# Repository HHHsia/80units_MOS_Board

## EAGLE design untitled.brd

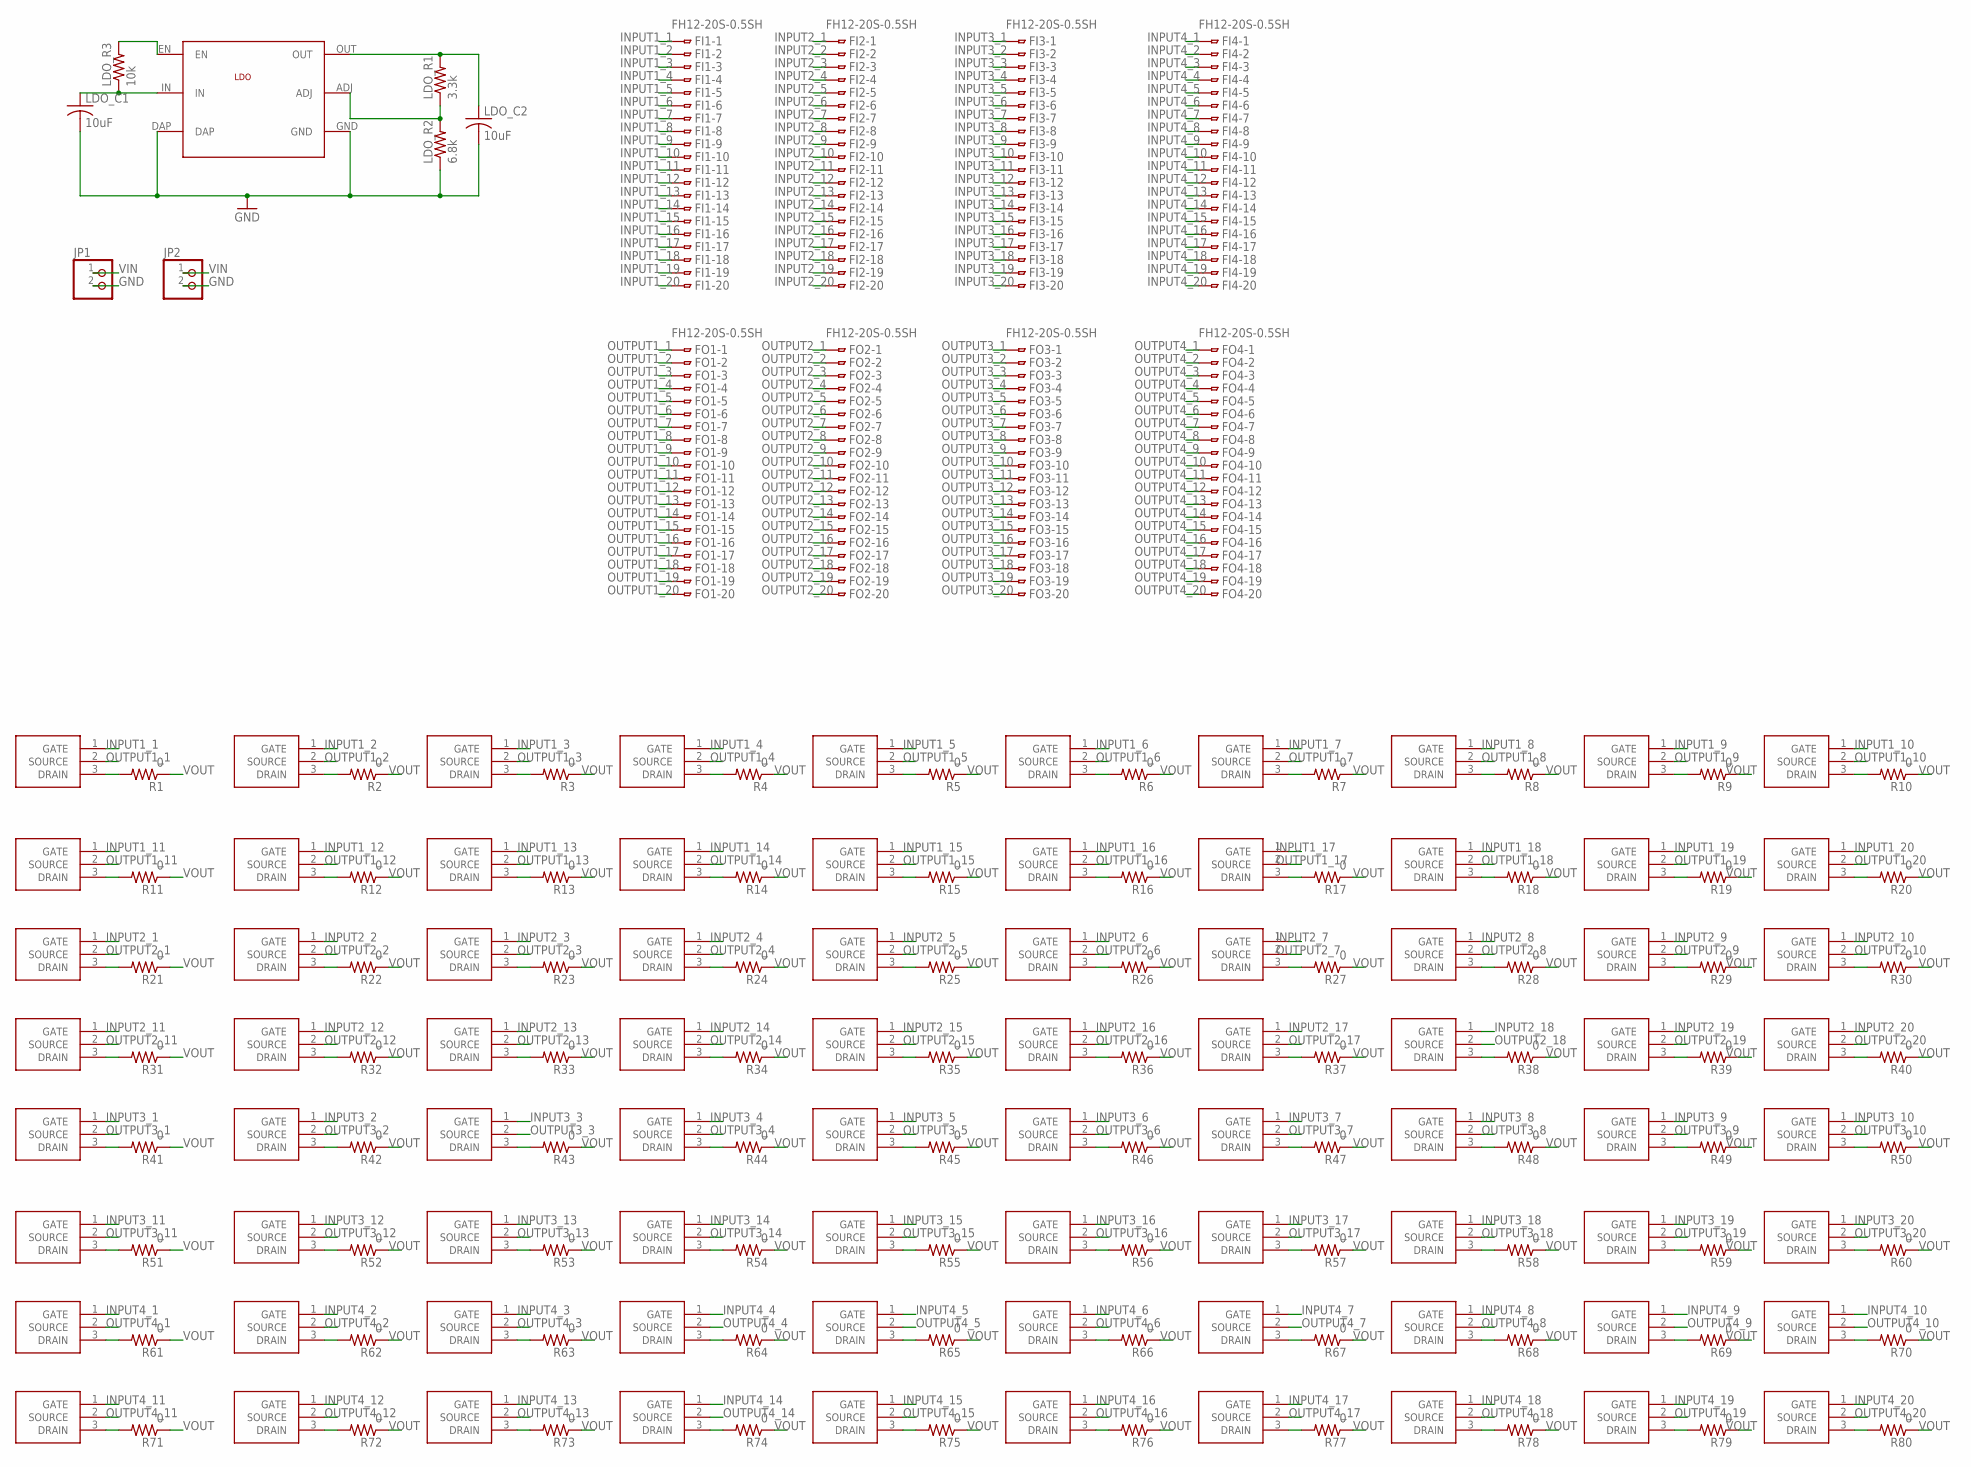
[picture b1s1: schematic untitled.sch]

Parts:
FI1, FI2, FI3, FI4: FH12-20S-0.5SH
FO1, FO2, FO3, FO4: FH12-20S-0.5SH
JP1, JP2: PINHD-1X2; 1X02
LDO: LP38501TS_ADJ
LDO_C1, LDO_C2: 10uF; C0805
LDO_R1: 3.3k; R0805
LDO_R2: 6.8k; R0805
LDO_R3: 10k; R0805
MOS1, MOS2, MOS3, MOS4, MOS5, MOS6, MOS7, MOS8, MOS9, MOS10, MOS11, MOS12, MOS13, MOS14, MOS15, MOS16, MOS17, MOS18, MOS19, MOS20, MOS21, MOS22, MOS23, MOS24, MOS25, MOS26, MOS27, MOS28, MOS29, MOS30, MOS31, MOS32, MOS33, MOS34, MOS35, MOS36, MOS37, MOS38, MOS39, MOS40, MOS41, MOS42, MOS43, MOS44, MOS45, MOS46, MOS47, MOS48, MOS49, MOS50, MOS51, MOS52, MOS53, MOS54, MOS55, MOS56, MOS57, MOS58, MOS59, MOS60, MOS61, MOS62, MOS63, MOS64, MOS65, MOS66, MOS67, MOS68, MOS69, MOS70, MOS71, MOS72, MOS73, MOS74, MOS75, MOS76, MOS77, MOS78, MOS79, MOS80: NX6008NBKNX6008NBK; SOT95P240X110-3N
R1, R2, R3, R4, R5, R6, R7, R8, R9, R10, R11, R12, R13, R14, R15, R16, R17, R18, R19, R20, R21, R22, R23, R24, R25, R26, R27, R28, R29, R30, R31, R32, R33, R34, R35, R36, R37, R38, R39, R40, R41, R42, R43, R44, R45, R46, R47, R48, R49, R50, R51, R52, R53, R54, R55, R56, R57, R58, R59, R60, R61, R62, R63, R64, R65, R66, R67, R68, R69, R70, R71, R72, R73, R74, R75, R76, R77, R78, R79, R80: 0; R0805

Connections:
GND: JP1.2, JP2.2, LDO.DAP, LDO.GND, LDO_C1.2, LDO_C2.2, LDO_R2.1
INPUT1_1: FI1.1, MOS1.1 (GATE)
INPUT1_2: FI1.2, MOS2.1 (GATE)
INPUT1_3: FI1.3, MOS3.1 (GATE)
INPUT1_4: FI1.4, MOS4.1 (GATE)
INPUT1_5: FI1.5, MOS5.1 (GATE)
INPUT1_6: FI1.6, MOS6.1 (GATE)
INPUT1_7: FI1.7, MOS7.1 (GATE)
INPUT1_8: FI1.8, MOS8.1 (GATE)
INPUT1_9: FI1.9, MOS9.1 (GATE)
INPUT1_10: FI1.10, MOS10.1 (GATE)
INPUT1_11: FI1.11, MOS11.1 (GATE)
INPUT1_12: FI1.12, MOS12.1 (GATE)
INPUT1_13: FI1.13, MOS13.1 (GATE)
INPUT1_14: FI1.14, MOS14.1 (GATE)
INPUT1_15: FI1.15, MOS15.1 (GATE)
INPUT1_16: FI1.16, MOS16.1 (GATE)
INPUT1_17: FI1.17, MOS17.1 (GATE)
INPUT1_18: FI1.18, MOS18.1 (GATE)
INPUT1_19: FI1.19, MOS19.1 (GATE)
INPUT1_20: FI1.20, MOS20.1 (GATE)
INPUT2_1: FI2.1, MOS21.1 (GATE)
INPUT2_2: FI2.2, MOS22.1 (GATE)
INPUT2_3: FI2.3, MOS23.1 (GATE)
INPUT2_4: FI2.4, MOS24.1 (GATE)
INPUT2_5: FI2.5, MOS25.1 (GATE)
INPUT2_6: FI2.6, MOS26.1 (GATE)
INPUT2_7: FI2.7, MOS27.1 (GATE)
INPUT2_8: FI2.8, MOS28.1 (GATE)
INPUT2_9: FI2.9, MOS29.1 (GATE)
INPUT2_10: FI2.10, MOS30.1 (GATE)
INPUT2_11: FI2.11, MOS31.1 (GATE)
INPUT2_12: FI2.12, MOS32.1 (GATE)
INPUT2_13: FI2.13, MOS33.1 (GATE)
INPUT2_14: FI2.14, MOS34.1 (GATE)
INPUT2_15: FI2.15, MOS35.1 (GATE)
INPUT2_16: FI2.16, MOS36.1 (GATE)
INPUT2_17: FI2.17, MOS37.1 (GATE)
INPUT2_18: FI2.18, MOS38.1 (GATE)
INPUT2_19: FI2.19, MOS39.1 (GATE)
INPUT2_20: FI2.20, MOS40.1 (GATE)
INPUT3_1: FI3.1, MOS41.1 (GATE)
INPUT3_2: FI3.2, MOS42.1 (GATE)
INPUT3_3: FI3.3, MOS43.1 (GATE)
INPUT3_4: FI3.4, MOS44.1 (GATE)
INPUT3_5: FI3.5, MOS45.1 (GATE)
INPUT3_6: FI3.6, MOS46.1 (GATE)
INPUT3_7: FI3.7, MOS47.1 (GATE)
INPUT3_8: FI3.8, MOS48.1 (GATE)
INPUT3_9: FI3.9, MOS49.1 (GATE)
INPUT3_10: FI3.10, MOS50.1 (GATE)
INPUT3_11: FI3.11, MOS51.1 (GATE)
INPUT3_12: FI3.12, MOS52.1 (GATE)
INPUT3_13: FI3.13, MOS53.1 (GATE)
INPUT3_14: FI3.14, MOS54.1 (GATE)
INPUT3_15: FI3.15, MOS55.1 (GATE)
INPUT3_16: FI3.16, MOS56.1 (GATE)
INPUT3_17: FI3.17, MOS57.1 (GATE)
INPUT3_18: FI3.18, MOS58.1 (GATE)
INPUT3_19: FI3.19, MOS59.1 (GATE)
INPUT3_20: FI3.20, MOS60.1 (GATE)
INPUT4_1: FI4.1, MOS61.1 (GATE)
INPUT4_2: FI4.2, MOS62.1 (GATE)
INPUT4_3: FI4.3, MOS63.1 (GATE)
INPUT4_4: FI4.4, MOS64.1 (GATE)
INPUT4_5: FI4.5, MOS65.1 (GATE)
INPUT4_6: FI4.6, MOS66.1 (GATE)
INPUT4_7: FI4.7, MOS67.1 (GATE)
INPUT4_8: FI4.8, MOS68.1 (GATE)
INPUT4_9: FI4.9, MOS69.1 (GATE)
INPUT4_10: FI4.10, MOS70.1 (GATE)
INPUT4_11: FI4.11, MOS71.1 (GATE)
INPUT4_12: FI4.12, MOS72.1 (GATE)
INPUT4_13: FI4.13, MOS73.1 (GATE)
INPUT4_14: FI4.14, MOS74.1 (GATE)
INPUT4_15: FI4.15, MOS75.1 (GATE)
INPUT4_16: FI4.16, MOS76.1 (GATE)
INPUT4_17: FI4.17, MOS77.1 (GATE)
INPUT4_18: FI4.18, MOS78.1 (GATE)
INPUT4_19: FI4.19, MOS79.1 (GATE)
INPUT4_20: FI4.20, MOS80.1 (GATE)
unnamed: LDO.EN, LDO_R3.2
unnamed: MOS77.3 (DRAIN), R77.2
unnamed: LDO.ADJ, LDO_R1.1, LDO_R2.2
unnamed: MOS1.3 (DRAIN), R1.2
unnamed: MOS2.3 (DRAIN), R2.2
unnamed: MOS3.3 (DRAIN), R3.2
unnamed: MOS4.3 (DRAIN), R4.2
unnamed: MOS5.3 (DRAIN), R5.2
unnamed: MOS6.3 (DRAIN), R6.2
unnamed: MOS7.3 (DRAIN), R7.2
unnamed: MOS8.3 (DRAIN), R8.2
unnamed: MOS9.3 (DRAIN), R9.2
unnamed: MOS10.3 (DRAIN), R10.2
unnamed: MOS11.3 (DRAIN), R11.2
unnamed: MOS12.3 (DRAIN), R12.2
unnamed: MOS13.3 (DRAIN), R13.2
unnamed: MOS14.3 (DRAIN), R14.2
unnamed: MOS15.3 (DRAIN), R15.2
unnamed: MOS16.3 (DRAIN), R16.2
unnamed: MOS17.3 (DRAIN), R17.2
unnamed: MOS18.3 (DRAIN), R18.2
unnamed: MOS19.3 (DRAIN), R19.2
unnamed: MOS20.3 (DRAIN), R20.2
unnamed: MOS21.3 (DRAIN), R21.2
unnamed: MOS22.3 (DRAIN), R22.2
unnamed: MOS23.3 (DRAIN), R23.2
unnamed: MOS24.3 (DRAIN), R24.2
unnamed: MOS25.3 (DRAIN), R25.2
unnamed: MOS26.3 (DRAIN), R26.2
unnamed: MOS27.3 (DRAIN), R27.2
unnamed: MOS28.3 (DRAIN), R28.2
unnamed: MOS29.3 (DRAIN), R29.2
unnamed: MOS30.3 (DRAIN), R30.2
unnamed: MOS31.3 (DRAIN), R31.2
unnamed: MOS32.3 (DRAIN), R32.2
unnamed: MOS33.3 (DRAIN), R33.2
unnamed: MOS34.3 (DRAIN), R34.2
unnamed: MOS35.3 (DRAIN), R35.2
unnamed: MOS36.3 (DRAIN), R36.2
unnamed: MOS37.3 (DRAIN), R37.2
unnamed: MOS38.3 (DRAIN), R38.2
unnamed: MOS39.3 (DRAIN), R39.2
unnamed: MOS40.3 (DRAIN), R40.2
unnamed: MOS41.3 (DRAIN), R41.2
unnamed: MOS42.3 (DRAIN), R42.2
unnamed: MOS43.3 (DRAIN), R43.2
unnamed: MOS44.3 (DRAIN), R44.2
unnamed: MOS45.3 (DRAIN), R45.2
unnamed: MOS46.3 (DRAIN), R46.2
unnamed: MOS47.3 (DRAIN), R47.2
unnamed: MOS48.3 (DRAIN), R48.2
unnamed: MOS49.3 (DRAIN), R49.2
unnamed: MOS50.3 (DRAIN), R50.2
unnamed: MOS51.3 (DRAIN), R51.2
unnamed: MOS52.3 (DRAIN), R52.2
unnamed: MOS53.3 (DRAIN), R53.2
unnamed: MOS54.3 (DRAIN), R54.2
unnamed: MOS55.3 (DRAIN), R55.2
unnamed: MOS56.3 (DRAIN), R56.2
unnamed: MOS57.3 (DRAIN), R57.2
unnamed: MOS58.3 (DRAIN), R58.2
unnamed: MOS59.3 (DRAIN), R59.2
unnamed: MOS60.3 (DRAIN), R60.2
unnamed: MOS61.3 (DRAIN), R61.2
unnamed: MOS62.3 (DRAIN), R62.2
unnamed: MOS63.3 (DRAIN), R63.2
unnamed: MOS64.3 (DRAIN), R64.2
unnamed: MOS65.3 (DRAIN), R65.2
unnamed: MOS66.3 (DRAIN), R66.2
unnamed: MOS67.3 (DRAIN), R67.2
unnamed: MOS68.3 (DRAIN), R68.2
unnamed: MOS69.3 (DRAIN), R69.2
unnamed: MOS70.3 (DRAIN), R70.2
unnamed: MOS71.3 (DRAIN), R71.2
unnamed: MOS72.3 (DRAIN), R72.2
unnamed: MOS73.3 (DRAIN), R73.2
unnamed: MOS74.3 (DRAIN), R74.2
unnamed: MOS75.3 (DRAIN), R75.2
unnamed: MOS76.3 (DRAIN), R76.2
unnamed: MOS78.3 (DRAIN), R78.2
unnamed: MOS79.3 (DRAIN), R79.2
unnamed: MOS80.3 (DRAIN), R80.2
OUTPUT1_1: FO1.1, MOS1.2 (SOURCE)
OUTPUT1_2: FO1.2, MOS2.2 (SOURCE)
OUTPUT1_3: FO1.3, MOS3.2 (SOURCE)
OUTPUT1_4: FO1.4, MOS4.2 (SOURCE)
OUTPUT1_5: FO1.5, MOS5.2 (SOURCE)
OUTPUT1_6: FO1.6, MOS6.2 (SOURCE)
OUTPUT1_7: FO1.7, MOS7.2 (SOURCE)
OUTPUT1_8: FO1.8, MOS8.2 (SOURCE)
OUTPUT1_9: FO1.9, MOS9.2 (SOURCE)
OUTPUT1_10: FO1.10, MOS10.2 (SOURCE)
OUTPUT1_11: FO1.11, MOS11.2 (SOURCE)
OUTPUT1_12: FO1.12, MOS12.2 (SOURCE)
OUTPUT1_13: FO1.13, MOS13.2 (SOURCE)
OUTPUT1_14: FO1.14, MOS14.2 (SOURCE)
OUTPUT1_15: FO1.15, MOS15.2 (SOURCE)
OUTPUT1_16: FO1.16, MOS16.2 (SOURCE)
OUTPUT1_17: FO1.17, MOS17.2 (SOURCE)
OUTPUT1_18: FO1.18, MOS18.2 (SOURCE)
OUTPUT1_19: FO1.19, MOS19.2 (SOURCE)
OUTPUT1_20: FO1.20, MOS20.2 (SOURCE)
OUTPUT2_1: FO2.1, MOS21.2 (SOURCE)
OUTPUT2_2: FO2.2, MOS22.2 (SOURCE)
OUTPUT2_3: FO2.3, MOS23.2 (SOURCE)
OUTPUT2_4: FO2.4, MOS24.2 (SOURCE)
OUTPUT2_5: FO2.5, MOS25.2 (SOURCE)
OUTPUT2_6: FO2.6, MOS26.2 (SOURCE)
OUTPUT2_7: FO2.7, MOS27.2 (SOURCE)
OUTPUT2_8: FO2.8, MOS28.2 (SOURCE)
OUTPUT2_9: FO2.9, MOS29.2 (SOURCE)
OUTPUT2_10: FO2.10, MOS30.2 (SOURCE)
OUTPUT2_11: FO2.11, MOS31.2 (SOURCE)
OUTPUT2_12: FO2.12, MOS32.2 (SOURCE)
OUTPUT2_13: FO2.13, MOS33.2 (SOURCE)
OUTPUT2_14: FO2.14, MOS34.2 (SOURCE)
OUTPUT2_15: FO2.15, MOS35.2 (SOURCE)
OUTPUT2_16: FO2.16, MOS36.2 (SOURCE)
OUTPUT2_17: FO2.17, MOS37.2 (SOURCE)
OUTPUT2_18: FO2.18, MOS38.2 (SOURCE)
OUTPUT2_19: FO2.19, MOS39.2 (SOURCE)
OUTPUT2_20: FO2.20, MOS40.2 (SOURCE)
OUTPUT3_1: FO3.1, MOS41.2 (SOURCE)
OUTPUT3_2: FO3.2, MOS42.2 (SOURCE)
OUTPUT3_3: FO3.3, MOS43.2 (SOURCE)
OUTPUT3_4: FO3.4, MOS44.2 (SOURCE)
OUTPUT3_5: FO3.5, MOS45.2 (SOURCE)
OUTPUT3_6: FO3.6, MOS46.2 (SOURCE)
OUTPUT3_7: FO3.7, MOS47.2 (SOURCE)
OUTPUT3_8: FO3.8, MOS48.2 (SOURCE)
OUTPUT3_9: FO3.9, MOS49.2 (SOURCE)
OUTPUT3_10: FO3.10, MOS50.2 (SOURCE)
OUTPUT3_11: FO3.11, MOS51.2 (SOURCE)
OUTPUT3_12: FO3.12, MOS52.2 (SOURCE)
OUTPUT3_13: FO3.13, MOS53.2 (SOURCE)
OUTPUT3_14: FO3.14, MOS54.2 (SOURCE)
OUTPUT3_15: FO3.15, MOS55.2 (SOURCE)
OUTPUT3_16: FO3.16, MOS56.2 (SOURCE)
OUTPUT3_17: FO3.17, MOS57.2 (SOURCE)
OUTPUT3_18: FO3.18, MOS58.2 (SOURCE)
OUTPUT3_19: FO3.19, MOS59.2 (SOURCE)
OUTPUT3_20: FO3.20, MOS60.2 (SOURCE)
OUTPUT4_1: FO4.1, MOS61.2 (SOURCE)
OUTPUT4_2: FO4.2, MOS62.2 (SOURCE)
OUTPUT4_3: FO4.3, MOS63.2 (SOURCE)
OUTPUT4_4: FO4.4, MOS64.2 (SOURCE)
OUTPUT4_5: FO4.5, MOS65.2 (SOURCE)
OUTPUT4_6: FO4.6, MOS66.2 (SOURCE)
OUTPUT4_7: FO4.7, MOS67.2 (SOURCE)
OUTPUT4_8: FO4.8, MOS68.2 (SOURCE)
OUTPUT4_9: FO4.9, MOS69.2 (SOURCE)
OUTPUT4_10: FO4.10, MOS70.2 (SOURCE)
OUTPUT4_11: FO4.11, MOS71.2 (SOURCE)
OUTPUT4_12: FO4.12, MOS72.2 (SOURCE)
OUTPUT4_13: FO4.13, MOS73.2 (SOURCE)
OUTPUT4_14: FO4.14, MOS74.2 (SOURCE)
OUTPUT4_15: FO4.15, MOS75.2 (SOURCE)
OUTPUT4_16: FO4.16, MOS76.2 (SOURCE)
OUTPUT4_17: FO4.17, MOS77.2 (SOURCE)
OUTPUT4_18: FO4.18, MOS78.2 (SOURCE)
OUTPUT4_19: FO4.19, MOS79.2 (SOURCE)
OUTPUT4_20: FO4.20, MOS80.2 (SOURCE)
VIN: JP1.1, JP2.1, LDO.IN, LDO_C1.1, LDO_R3.1
VOUT: LDO.OUT, LDO_C2.1, LDO_R1.2, R1.1, R2.1, R3.1, R4.1, R5.1, R6.1, R7.1, R8.1, R9.1, R10.1, R11.1, R12.1, R13.1, R14.1, R15.1, R16.1, R17.1, R18.1, R19.1, R20.1, R21.1, R22.1, R23.1, R24.1, R25.1, R26.1, R27.1, R28.1, R29.1, R30.1, R31.1, R32.1, R33.1, R34.1, R35.1, R36.1, R37.1, R38.1, R39.1, R40.1, R41.1, R42.1, R43.1, R44.1, R45.1, R46.1, R47.1, R48.1, R49.1, R50.1, R51.1, R52.1, R53.1, R54.1, R55.1, R56.1, R57.1, R58.1, R59.1, R60.1, R61.1, R62.1, R63.1, R64.1, R65.1, R66.1, R67.1, R68.1, R69.1, R70.1, R71.1, R72.1, R73.1, R74.1, R75.1, R76.1, R77.1, R78.1, R79.1, R80.1

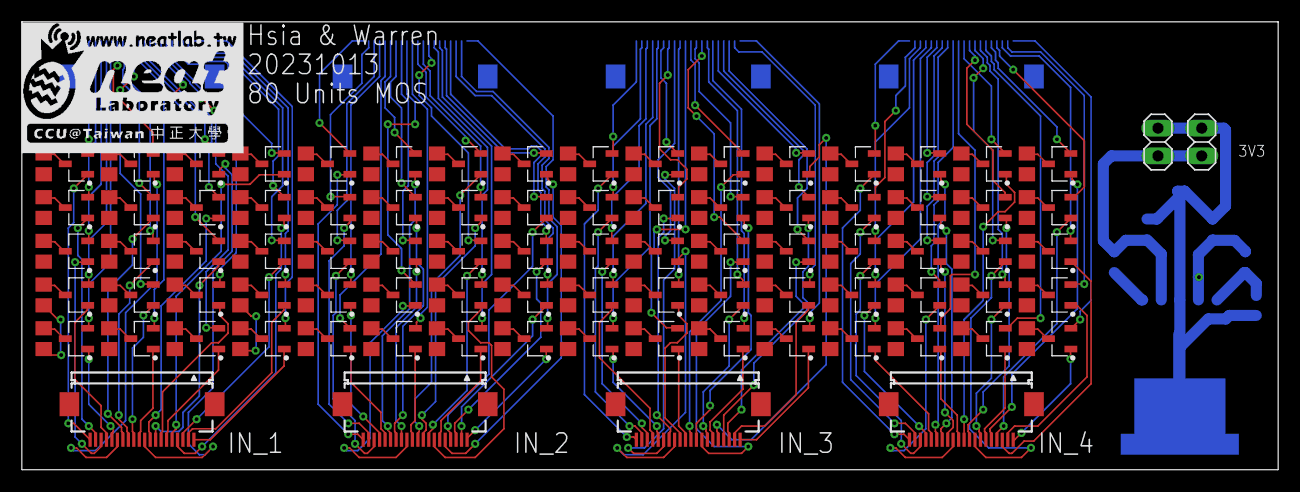
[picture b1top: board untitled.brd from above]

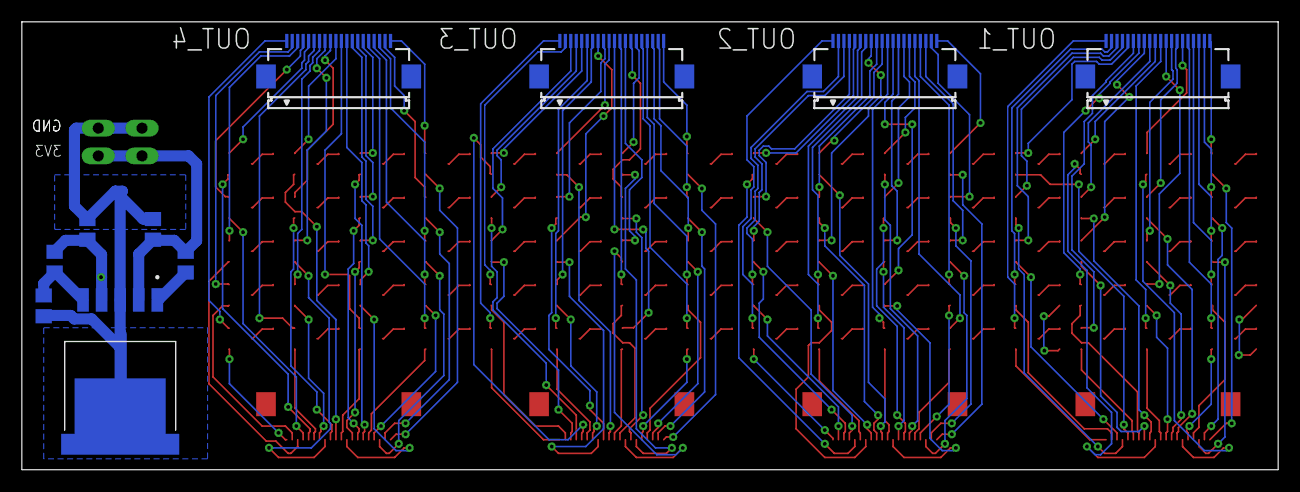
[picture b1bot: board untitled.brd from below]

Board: 2 copper layers, 115.0 x 41.0 mm, 177 parts (10 on the bottom side), 245 nets.

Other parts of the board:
U$1: LOGO_SCALE_2.0

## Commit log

2024-07-05 0705
